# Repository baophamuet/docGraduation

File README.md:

# docGraduation
document Graduation
full doc

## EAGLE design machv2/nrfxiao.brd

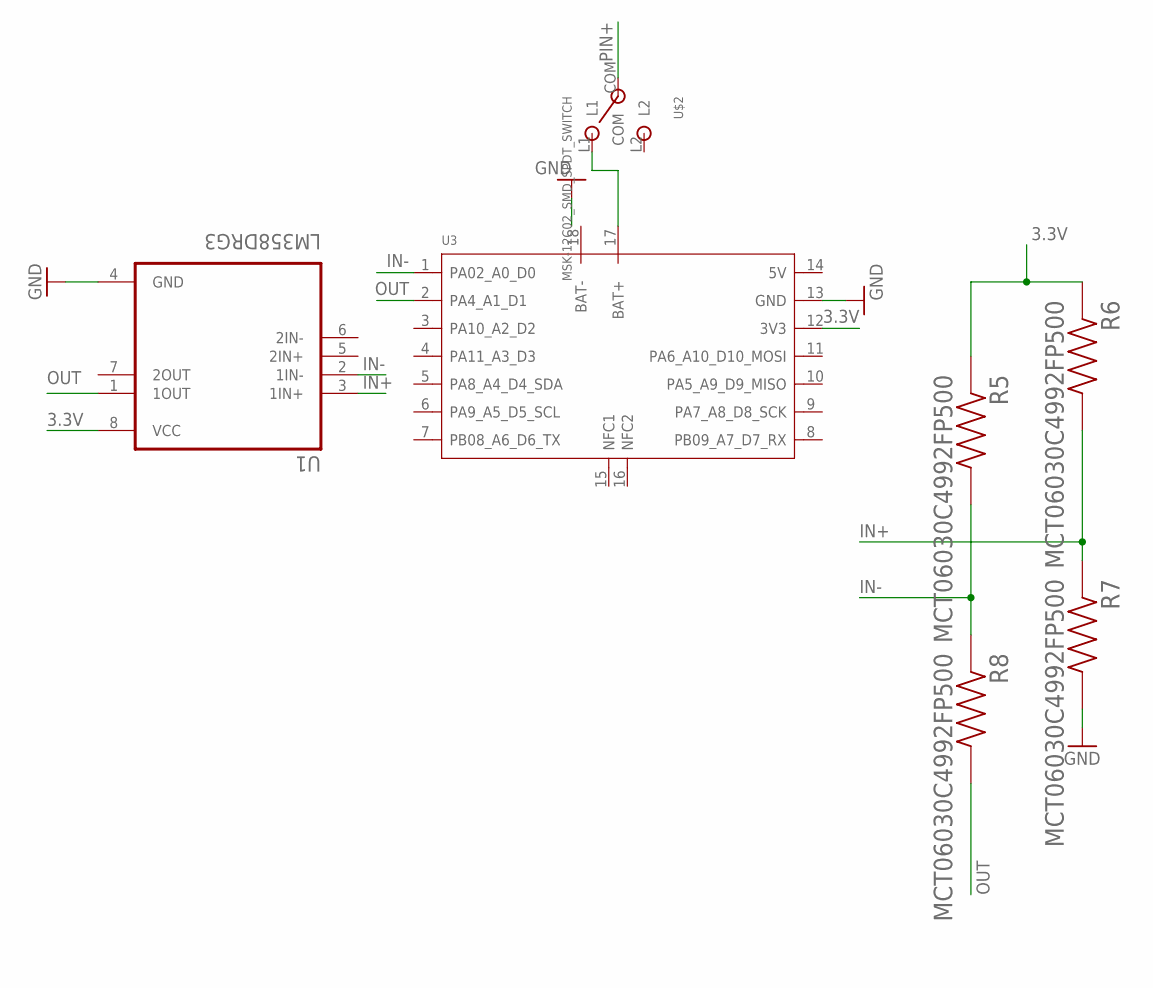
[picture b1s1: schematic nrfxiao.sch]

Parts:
R5, R6, R7, R8: MCT06030C4992FP500; RESC1508X55N
U1: LM358DRG3; SOIC127P599X175-8N
U3: MOUDLE-SEEEDUINO-XIAO-NRF52840-SENSE-SMD; MOUDLE16P-SMD-2.54-21X17.8MM
U$2: MSK-12C02_SMD_SPDT_SWITCH; MSK-12C02

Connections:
3.3V: R5.1, R6.1, U1.8 (VCC), U3.12 (3V3)
GND: R7.2, U1.4 (GND), U3.13 (GND)
IN+: R6.2, R7.1, U1.3 (1IN+)
IN-: R5.2, R8.1, U1.2 (1IN-), U3.1 (PA02_A0_D0)
unnamed: U3.17 (BAT+), U$2.L1
OUT: R8.2, U1.1 (1OUT), U3.2 (PA4_A1_D1)
PIN+: U$2.COM

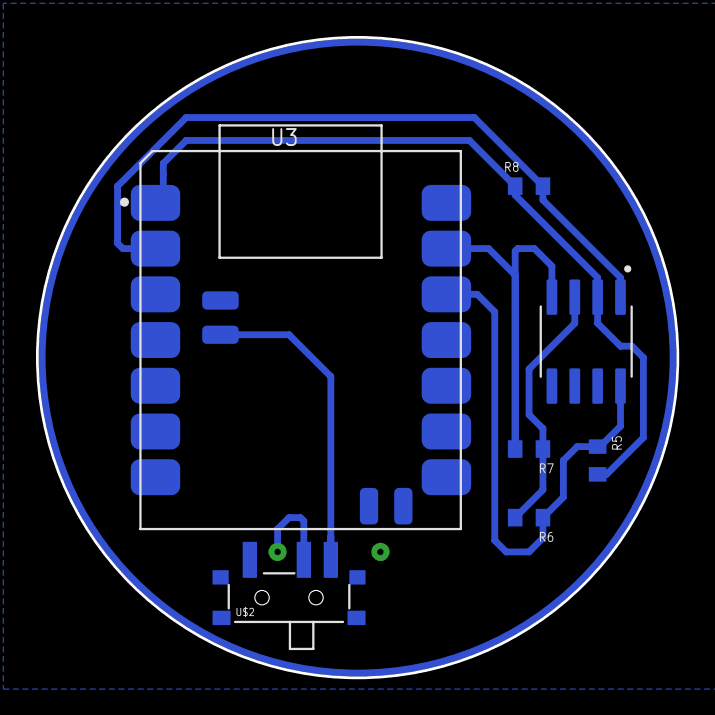
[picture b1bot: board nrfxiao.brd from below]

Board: 2 copper layers, 35.6 x 35.6 mm, 7 parts (7 on the bottom side), 6 nets.

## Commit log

2023-05-26 Doc Full commit
